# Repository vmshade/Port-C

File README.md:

# Port-C Rev2

## Updates to V2

- Removed unnessesary capacitors and resistors
- Added a PTC Fuse for better hot plugging support
- Made the board smaller
- Replaced the JST-SH port with the new Molex Pico-EZmate (As per Unified Daughterboard standards)

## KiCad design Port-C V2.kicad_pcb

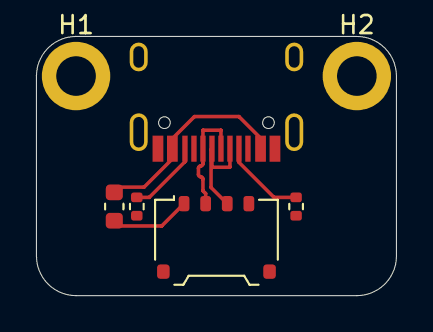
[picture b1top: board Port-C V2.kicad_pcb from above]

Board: 2 copper layers, 20.0 x 14.4 mm, 7 parts (0 on the bottom side), 7 nets.

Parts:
F1: 750mA; Fuse_0603_1608Metric
H1, H2: MountingHole_Pad; MountingHole_2.2mm_M2_DIN965_Pad
J1: USB_C_Receptacle_USB2.0_14P; USB_C_HRO_TYPE-C-31-M-12
J2: Conn_01x04_Socket; Molex_Pico-EZmate_78171-0004_1x04-1MP_P1.20mm_Vertical
R1, R2: 5.1k; R_0402_1005Metric

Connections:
D+: J1.A6 (D+), J1.B6 (D+), J2.2
D-: J1.A7 (D-), J1.B7 (D-), J2.3
GND: H1.1 (1_1), H2.1 (1_1), J1.A1 (GND), J1.A12 (GND), J1.B1 (GND), J1.B12 (GND), J2.4, R1.2, R2.1
unnamed: F1.1, J1.A4 (VBUS), J1.A9 (VBUS), J1.B4 (VBUS), J1.B9 (VBUS)
unnamed: J1.A5 (CC1), R1.1
unnamed: J1.B5 (CC2), R2.2
VBUS: F1.2, J2.1

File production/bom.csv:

Designator,Footprint,Quantity,Value,LCSC Part #
F1,0603,1,750mA,
J1,USB_C_HRO_TYPE-C-31-M-12,1,USB_C_Receptacle_USB2.0_14P,
J2,Molex_Pico-EZmate_78171-0004_1x04-1MP_P1.20mm_Vertical,1,Conn_01x04_Socket,
"R1, R2",0402,2,5.1k,

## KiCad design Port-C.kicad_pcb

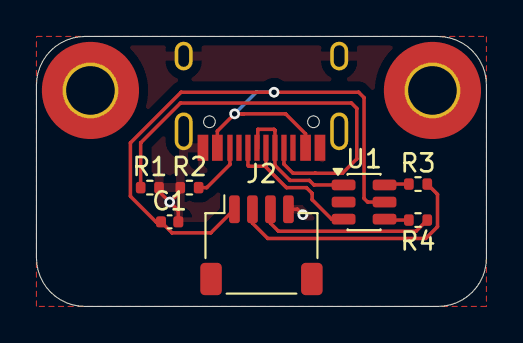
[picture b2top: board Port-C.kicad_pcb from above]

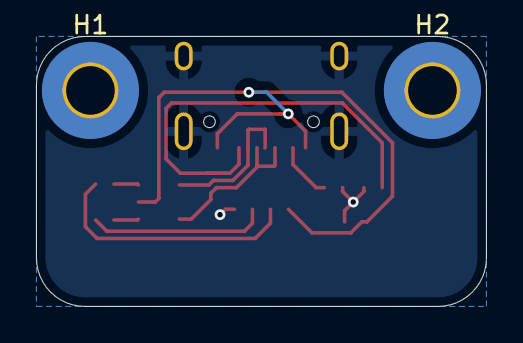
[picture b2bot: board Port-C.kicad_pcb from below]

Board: 2 copper layers, 25.0 x 15.0 mm, 10 parts (2 on the bottom side), 8 nets.

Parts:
C1: 10uF; C_0402_1005Metric
H1, H2: MountingHole_Pad; MountingHole_2.7mm_M2.5_Pad_TopBottom
J1: USB_C_Receptacle_USB2.0_14P; USB_C_HRO_TYPE-C-31-M-12
J2: Conn_01x04_Socket; JST_SH_SM04B-SRSS-TB_1x04-1MP_P1.00mm_Horizontal
R1, R2: 5.1k; R_0402_1005Metric
R3, R4: 27; R_0402_1005Metric
U1: USBLC6-2SC6; SOT-23-6

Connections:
+5V: C1.1, J1.A4 (VBUS), J1.A9 (VBUS), J1.B4 (VBUS), J1.B9 (VBUS), U1.5 (VBUS)
GND: C1.2, J1.A1 (GND), J1.A12 (GND), J1.B1 (GND), J1.B12 (GND), J1.S1 (SHIELD), J2.4, R1.2, R2.1, U1.2 (GND)
unnamed: J1.A5 (CC1), R1.1
unnamed: J1.B5 (CC2), R2.2
unnamed: R3.1, U1.6 (I/O1)
unnamed: R4.2, U1.4 (I/O2)
USB_D+: J1.A6 (D+), J1.B6 (D+), J2.3, R3.2, U1.1 (I/O1)
USB_D-: J1.A7 (D-), J1.B7 (D-), J2.2, R4.1, U1.3 (I/O2)

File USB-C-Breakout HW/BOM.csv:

"Reference","Qty","Value","DNP","Exclude from BOM","Exclude from Board","Footprint","Datasheet"
"H1,H2,H3,H4","4","MountingHole_Pad","","Excluded from BOM","","MountingHole:MountingHole_2.2mm_M2_Pad","~"
"J1","1","USB_C_Receptacle_USB2.0_14P","","","","Adafruit 2040:USB_C_Receptacle_HRO_TYPE-C-31-M-12","https://www.usb.org/sites/default/files/documents/usb_type-c.zip"
"J2","1","Conn_01x04_MountingPin","","","","Connector_JST:JST_PH_S4B-PH-K_1x04_P2.00mm_Horizontal","~"
"R1,R2","2","5.1K","","","","Resistor_SMD:R_0402_1005Metric","~"
"R3,R4","2","27","","","","Resistor_SMD:R_0402_1005Metric","~"

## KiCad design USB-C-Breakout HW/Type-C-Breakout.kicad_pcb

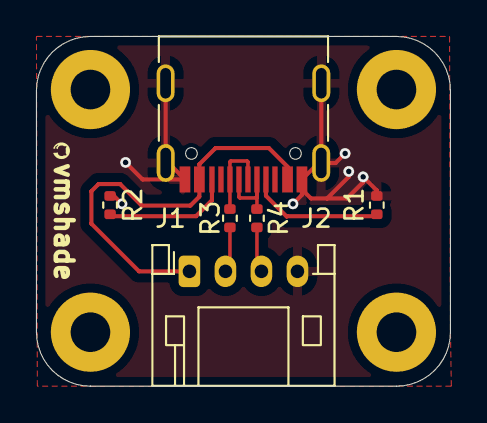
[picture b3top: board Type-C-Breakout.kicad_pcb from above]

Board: 2 copper layers, 23.0 x 19.4 mm, 10 parts (0 on the bottom side), 8 nets.

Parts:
H1, H2, H3, H4: MountingHole_Pad; MountingHole_2.2mm_M2_Pad
J1: USB_C_Receptacle_USB2.0_14P; USB_C_Receptacle_HRO_TYPE-C-31-M-12
J2: Conn_01x04_MountingPin; JST_PH_S4B-PH-K_1x04_P2.00mm_Horizontal
R1, R2: 5.1K; R_0402_1005Metric
R3, R4: 27; R_0402_1005Metric

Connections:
GND: J1.A1 (GND), J1.A12 (GND), J1.B1 (GND), J1.B12 (GND), J1.S1 (SHIELD), J2.4, R1.2, R2.1
unnamed: J1.A5 (CC1), R1.1
unnamed: J1.B5 (CC2), R2.2
unnamed: J2.2, R3.2
unnamed: J2.3, R4.1
USB_D+: J1.A6 (D+), J1.B6 (D+), R3.1
USB_D-: J1.A7 (D-), J1.B7 (D-), R4.2
VBUS: J1.A4 (VBUS), J1.A9 (VBUS), J1.B4 (VBUS), J1.B9 (VBUS), J2.1

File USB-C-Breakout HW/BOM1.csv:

Reference,Qty,Value,Price,Links To Parts
"H1,H2,H3,H4",4,MountingHole_Pad,N/A,N/A
J1,1,USB_C_Receptacle_USB2.0_14P, £0.14 ,https://jlcpcb.com/partdetail/Korean_HropartsElec-TYPE_C_31_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
J2,1,JST 4 pin PH 2.00mm, £0.04 ,https://jlcpcb.com/partdetail/JST-S4B_PH_K_S_LF_SN/C157926
"R1,R2",2,5.1K, £0.01 ,https://jlcpcb.com/partdetail/26648-0402WGF5101TCE/C25905
"R3,R4",2,27, £0.01 ,https://jlcpcb.com/partdetail/25843-0402WGF270JTCE/C25100
PCB,1,N/A, £7.27 ,N/A
TOTAL,,, £7.47 ,

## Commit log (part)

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2026-03-26 Added Files :D
2026-03-26 More files :)
2026-03-26 dasodfjkl
2026-03-26 sdjkdjaskda
2026-04-04 Replaced the Files
2026-04-04 Updated Files
2026-04-04 Add README for Port-C daughterboard
    Added project description and features for Port-C daughterboard.
2026-04-04 Update README with schematic and PCB images
    Added images for schematic, PCB, and PCB render.
